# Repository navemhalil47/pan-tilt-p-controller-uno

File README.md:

# Single-Axis Target Tracker

An Arduino-based closed-loop control system that autonomously tracks a light source using a proportional control algorithm. This project serves as the foundational mechanical and algorithmic proof-of-concept for a future autonomous pan-tilt target tracking turret.

## Features
* **Proportional (P) Controller:** Calculates the error margin between two LDR sensors and dynamically adjusts the stepper motor's step size for smooth, jitter-free targeting.
* **Real-Time Telemetry:** Outputs sensor readings and error (deviation) margins continuously to the Serial Monitor.
* **Hardware Setup:** Utilizes an Arduino Uno, a 28BYJ-48 Stepper Motor with ULN2003 driver, and photoresistors in a voltage divider configuration.

## Components
* Arduino Uno
* 28BYJ-48 Stepper Motor & ULN2003 Driver Board
* 2x LDR (Photoresistors) & Resistors
* Breadboard and Jumper Wires

## Future Work
This single-axis mechanism is designed to be upgraded into a dual-axis (pan-tilt) autonomous tracking turret prototype. Future iterations will replace the LDR sensor array with camera-based computer vision tracking algorithms.

## (you can use with breadboard or pcb format)

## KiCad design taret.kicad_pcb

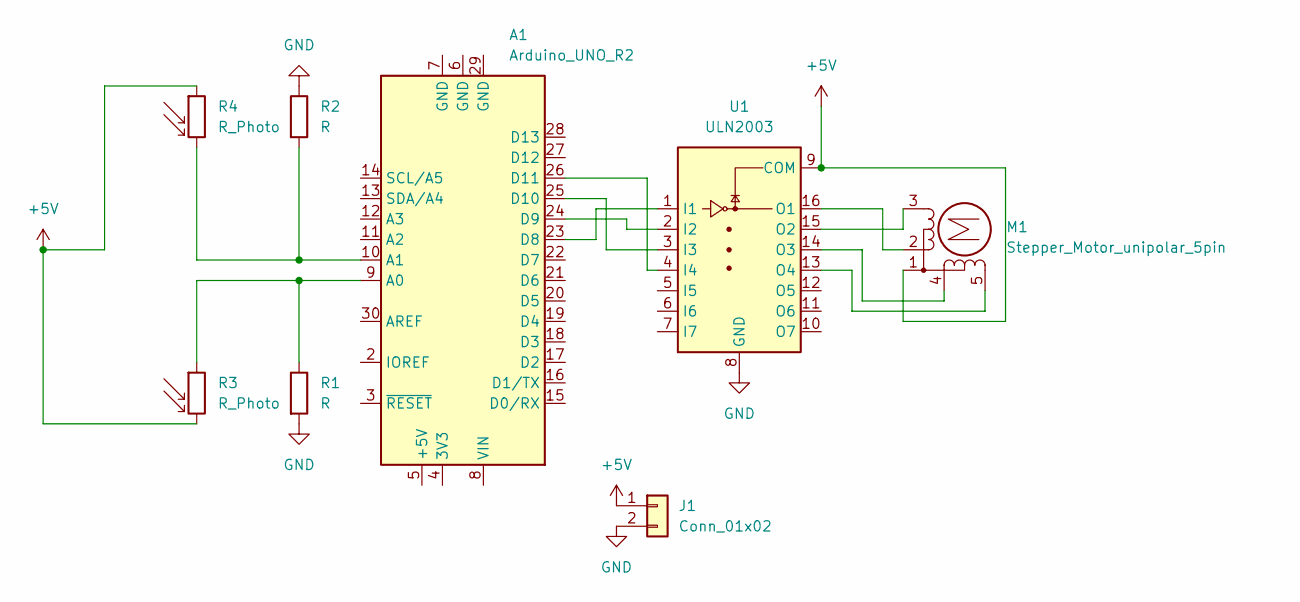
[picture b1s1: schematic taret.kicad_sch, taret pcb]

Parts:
A1: Arduino_UNO_R2
J1: Conn_01x02; TerminalBlock_Phoenix_MKDS-1,5-2-5.08_1x02_P5.08mm_Horizont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
M1: Stepper_Motor_unipolar_5pin; PinHeader_1x05_P2.54mm_Vertical
R1, R2: R; R_Axial_DIN0207_L6.3mm_D2.5mm_P10.16mm_Horizontal
R3, R4: R_Photo; R_LDR_5.1x4.3mm_P3.4mm_Vertical
U1: ULN2003; DIP-16_W7.62mm

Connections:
+5V: J1.1, M1.1, R3.2, R4.1, U1.9 (COM)
GND: J1.2, R1.2, R2.1, U1.8 (GND)
unnamed: A1.9 (A0), R1.1, R3.1
unnamed: A1.10 (A1), R2.2, R4.2
unnamed: A1.23 (D8), U1.1 (I1)
unnamed: A1.24 (D9), U1.2 (I2)
unnamed: A1.25 (D10), U1.3 (I3)
unnamed: A1.26 (D11), U1.4 (I4)
unnamed: M1.3 (-_3), U1.15 (O2)
unnamed: M1.2, U1.16 (O1)
unnamed: M1.4, U1.14 (O3)
unnamed: M1.5, U1.13 (O4)

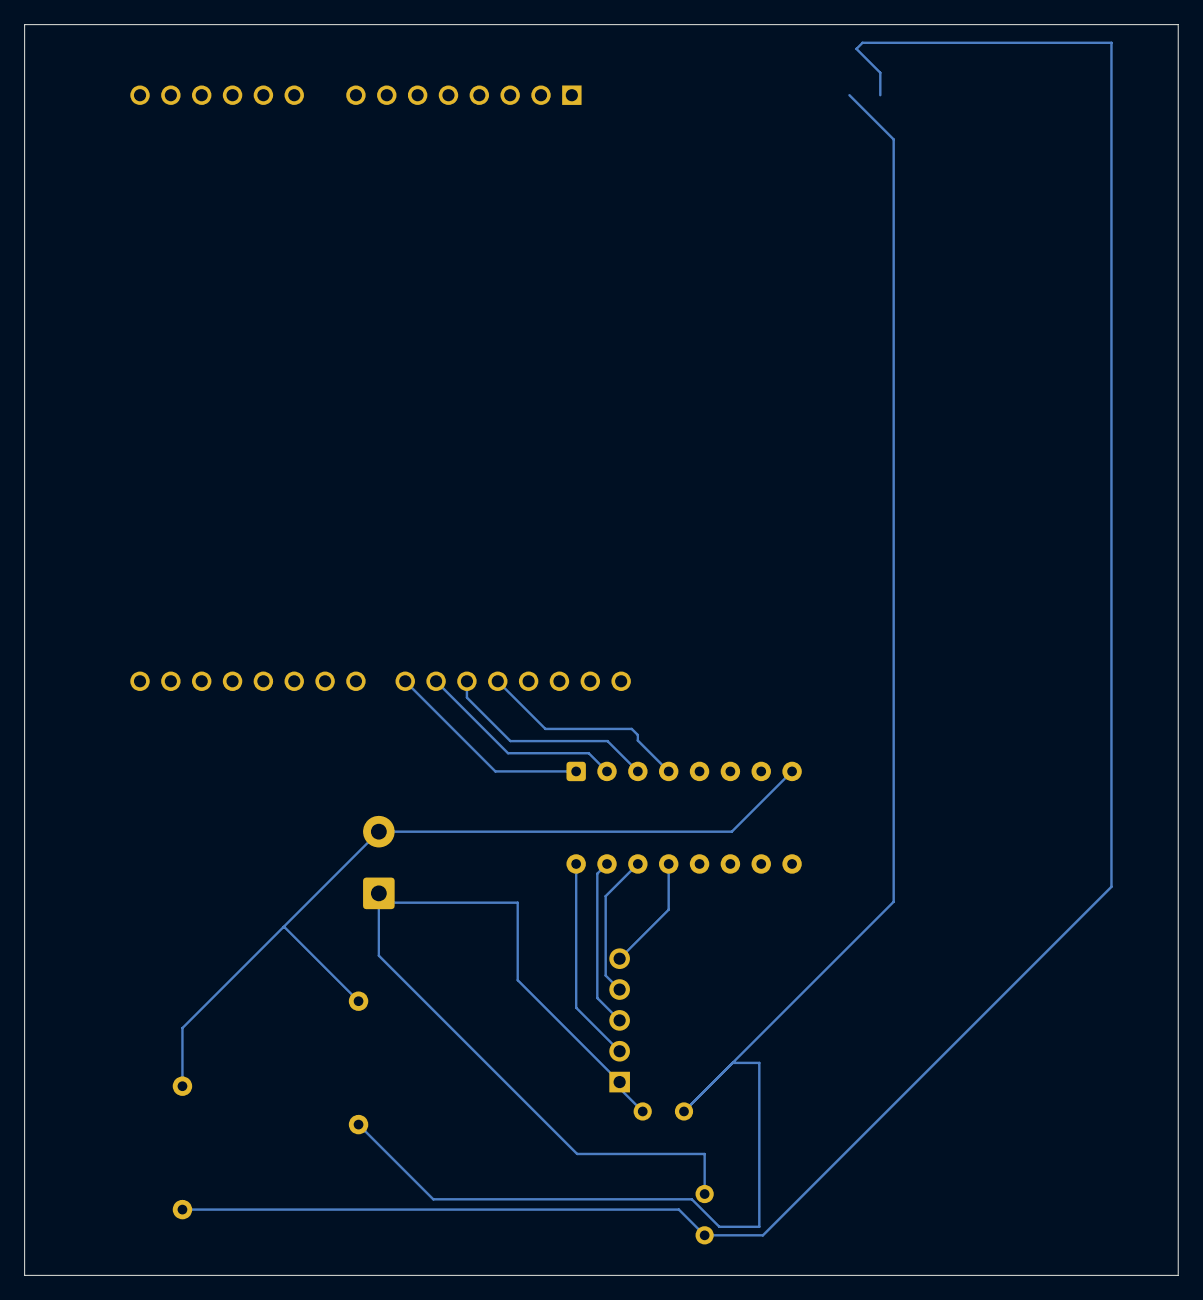
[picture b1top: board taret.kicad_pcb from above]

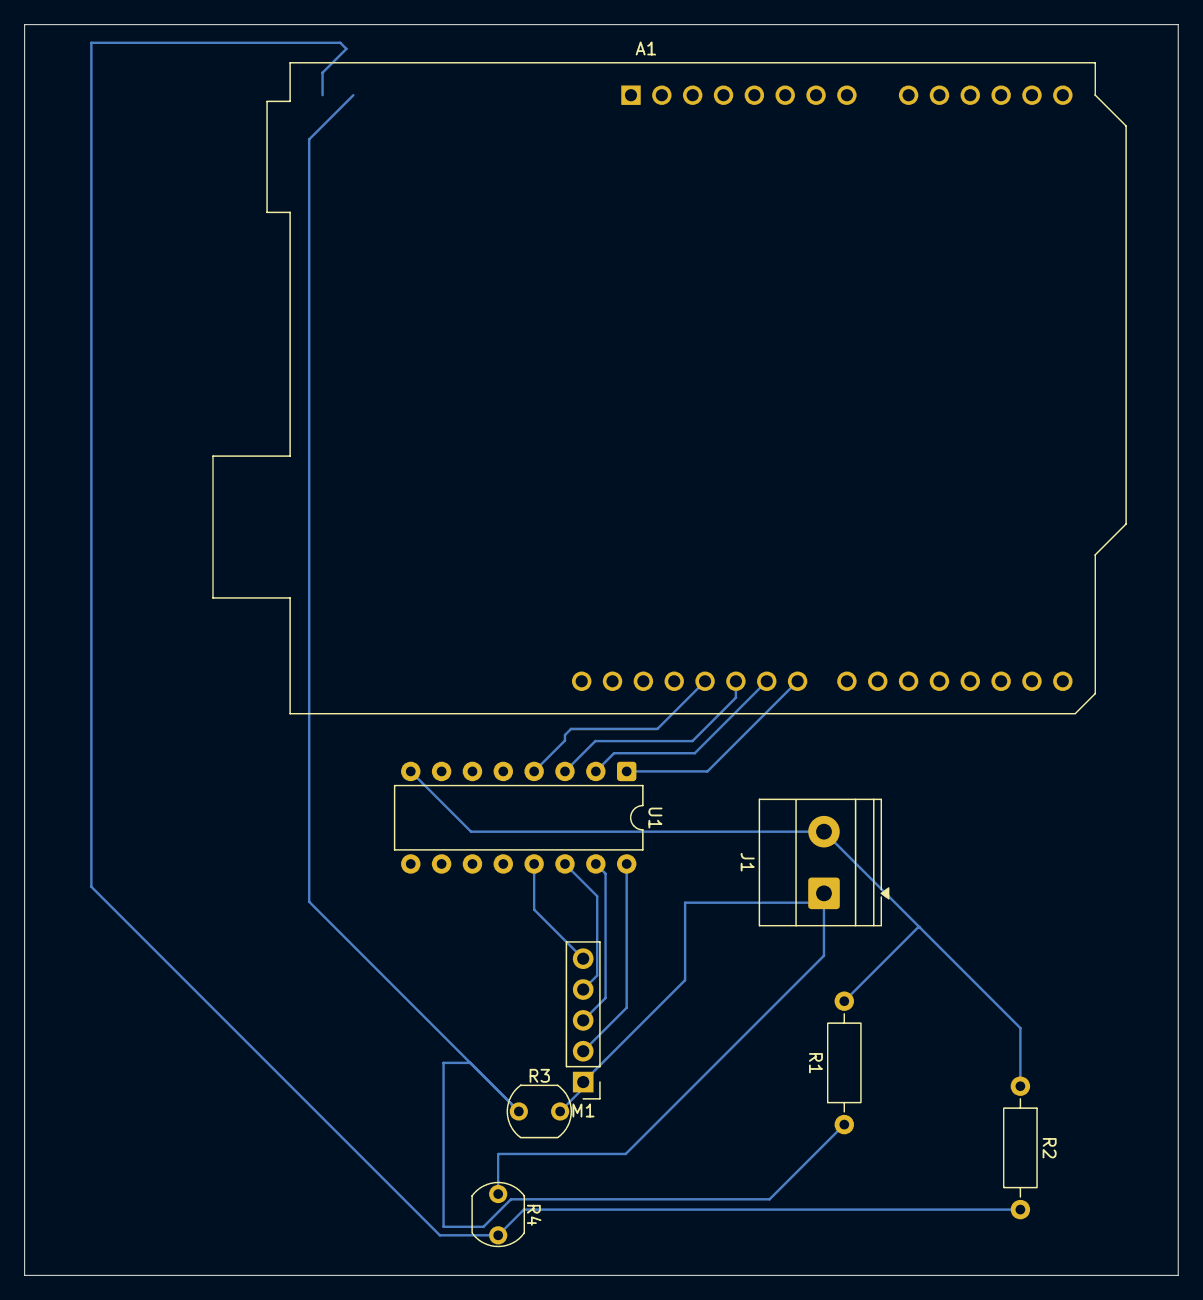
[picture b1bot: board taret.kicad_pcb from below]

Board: 2 copper layers, 95.0 x 103.0 mm, 8 parts (8 on the bottom side), 12 nets.
